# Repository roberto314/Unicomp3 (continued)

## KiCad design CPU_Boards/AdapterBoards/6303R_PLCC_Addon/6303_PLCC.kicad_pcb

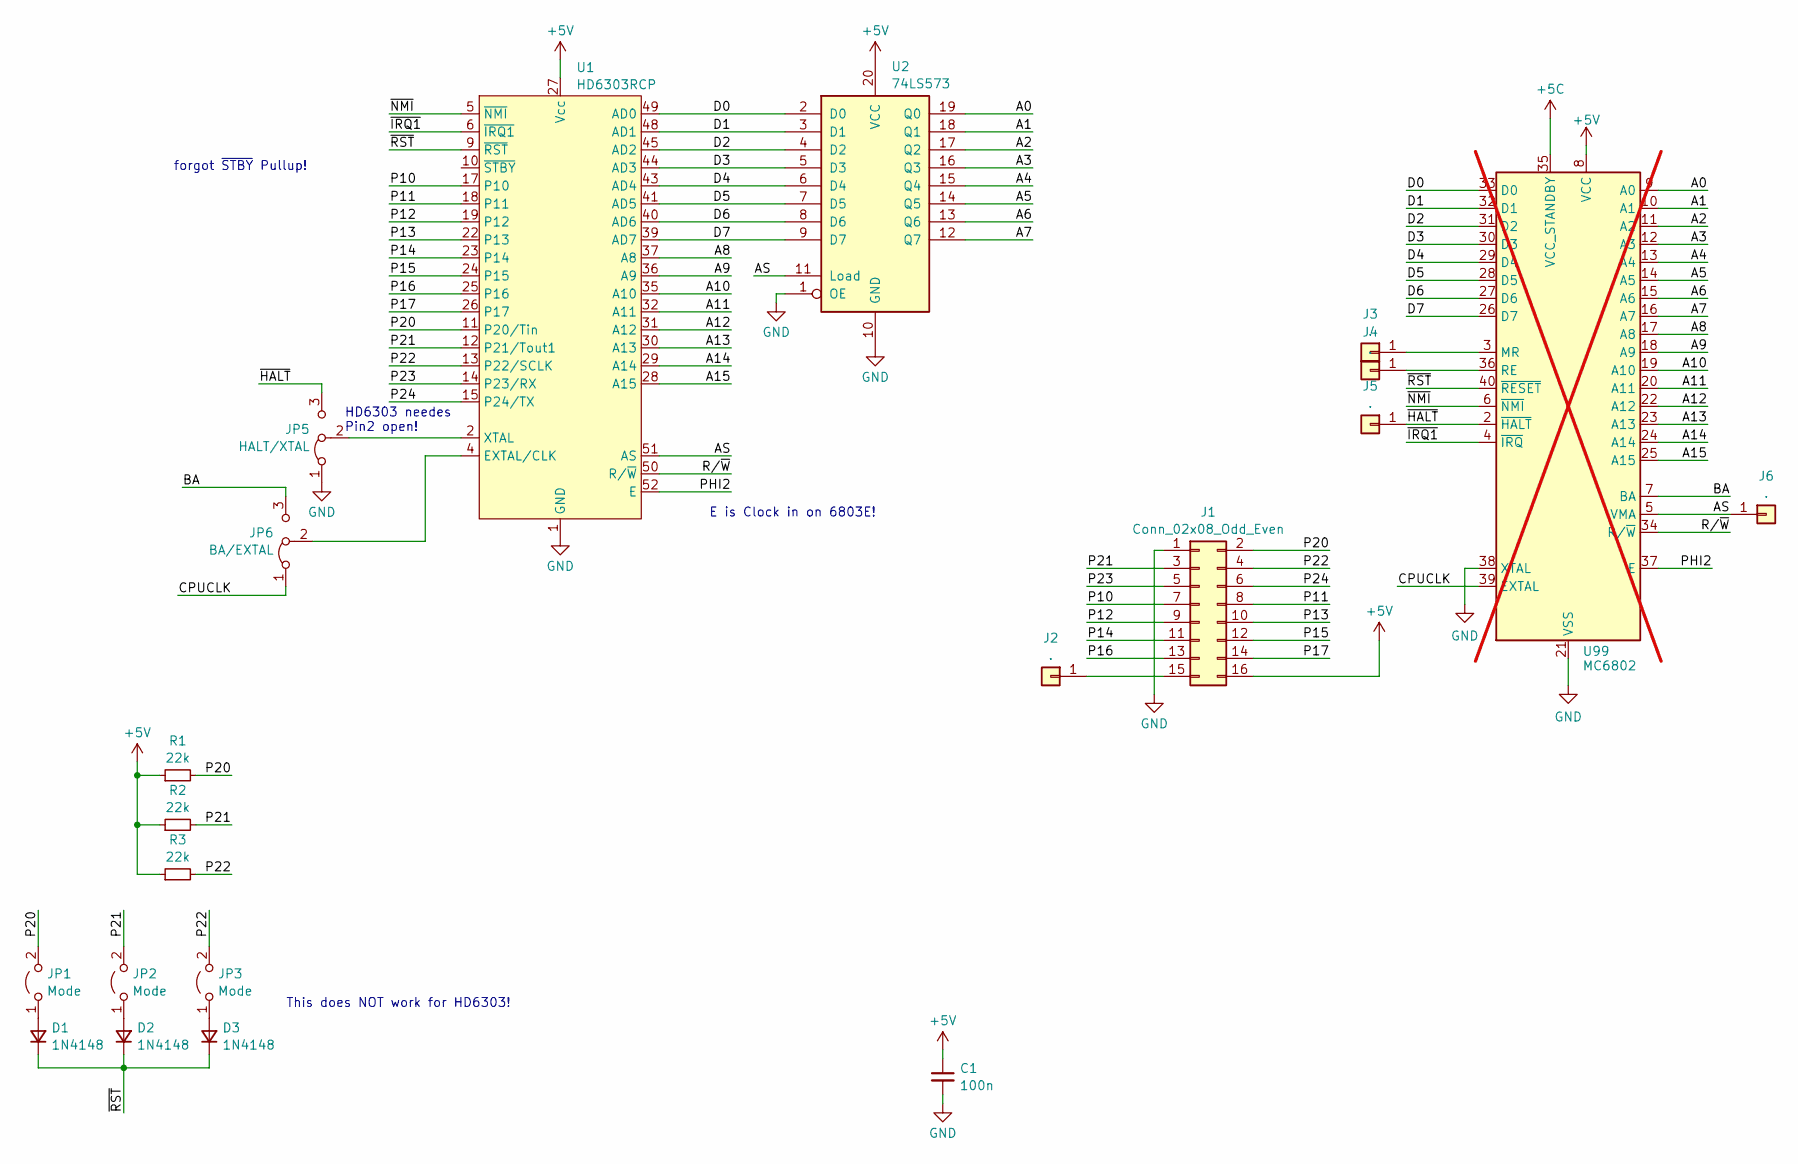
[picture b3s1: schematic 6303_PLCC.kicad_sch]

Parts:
C1: 100n; C_1206_3216Metric_Pad1.33x1.80mm_HandSolder
D1, D2, D3: 1N4148; D_1206_3216Metric_Pad1.42x1.75mm_HandSolder
J1: Conn_02x08_Odd_Even; PinHeader_2x08_P2.54mm_Horizontal
J2, J3, J4, J5, J6: .; PinHeader_1x01_P2.00mm_Vertical
JP1, JP2, JP3: Mode; PinHeader_1x02_P2.54mm_Vertical
JP5: HALT/XTAL; PinHeader_1x03_P2.54mm_Vertical
JP6: BA/EXTAL; PinHeader_1x03_P2.54mm_Vertical
R1, R2, R3: 22k; R_1206_3216Metric_Pad1.30x1.75mm_HandSolder
U1: HD6303RCP; PLCC-52_SMD-Socket
U2: 74LS573; DIP-20_W7.62mm_Socket_LongPads
U99: MC6802; DIP-40_W15.24mm; not fitted

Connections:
+5V: C1.1, J1.16, R1.1, R2.1, R3.1, U1.27 (Vcc), U2.20 (VCC); also elsewhere on the board
/A0: U2.19 (Q0); also elsewhere on the board
/A1: U2.18 (Q1); also elsewhere on the board
/A2: U2.17 (Q2); also elsewhere on the board
/A3: U2.16 (Q3); also elsewhere on the board
/A4: U2.15 (Q4); also elsewhere on the board
/A5: U2.14 (Q5); also elsewhere on the board
/A6: U2.13 (Q6); also elsewhere on the board
/A7: U2.12 (Q7); also elsewhere on the board
/A8: U1.37 (A8); also elsewhere on the board
/A9: U1.36 (A9); also elsewhere on the board
/A10: U1.35 (A10); also elsewhere on the board
/A11: U1.32 (A11); also elsewhere on the board
/A12: U1.31 (A12); also elsewhere on the board
/A13: U1.30 (A13); also elsewhere on the board
/A14: U1.29 (A14); also elsewhere on the board
/A15: U1.28 (A15); also elsewhere on the board
/AS: J6.1, U1.51 (AS), U2.11 (Load); also elsewhere on the board
/BA: JP6.3 (B); also elsewhere on the board
/CPUCLK: JP6.1 (A); also elsewhere on the board
/D0: U1.49 (AD0), U2.2 (D0); also elsewhere on the board
/D1: U1.48 (AD1), U2.3 (D1); also elsewhere on the board
/D2: U1.45 (AD2), U2.4 (D2); also elsewhere on the board
/D3: U1.44 (AD3), U2.5 (D3); also elsewhere on the board
/D4: U1.43 (AD4), U2.6 (D4); also elsewhere on the board
/D5: U1.41 (AD5), U2.7 (D5); also elsewhere on the board
/D6: U1.40 (AD6), U2.8 (D6); also elsewhere on the board
/D7: U1.39 (AD7), U2.9 (D7); also elsewhere on the board
/P10: J1.7, U1.17 (P10)
/P11: J1.8, U1.18 (P11)
/P12: J1.9, U1.19 (P12)
/P13: J1.10, U1.22 (P13)
/P14: J1.11, U1.23 (P14)
/P15: J1.12, U1.24 (P15)
/P16: J1.13, U1.25 (P16)
/P17: J1.14, U1.26 (P17)
/P20: J1.2, JP1.2 (B), R1.2, U1.11 (P20/Tin)
/P21: J1.3, JP2.2 (B), R2.2, U1.12 (P21/Tout1)
/P22: J1.4, JP3.2 (B), R3.2, U1.13 (P22/SCLK)
/P23: J1.5, U1.14 (P23/RX)
/P24: J1.6, U1.15 (P24/TX)
/PHI2: U1.52 (E); also elsewhere on the board
/R/~W: U1.50 (R/~W); also elsewhere on the board
/~HALT: J5.1, JP5.3 (B); also elsewhere on the board
/~IRQ1: U1.6 (~IRQ1); also elsewhere on the board
/~NMI: U1.5 (~NMI); also elsewhere on the board
/~RST: D1.1 (K), D2.1 (K), D3.1 (K), U1.9 (~RST); also elsewhere on the board
GND: C1.2, J1.1, JP5.1 (A), U1.1 (GND), U2.1 (OE), U2.10 (GND); also elsewhere on the board
unnamed: D1.2 (A), JP1.1 (A)
unnamed: D2.2 (A), JP2.1 (A)
unnamed: D3.2 (A), JP3.1 (A)
unnamed: J1.15, J2.1
unnamed 53: J3.1; also elsewhere on the board
unnamed 54: J4.1; also elsewhere on the board
unnamed: JP5.2 (C), U1.2 (XTAL)
unnamed: JP6.2 (C), U1.4 (EXTAL/CLK)

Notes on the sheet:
forgot ~{STBY} Pullup!
This does NOT work for HD6303!
E is Clock in on 6803E!
HD6303 needes Pin2 open!

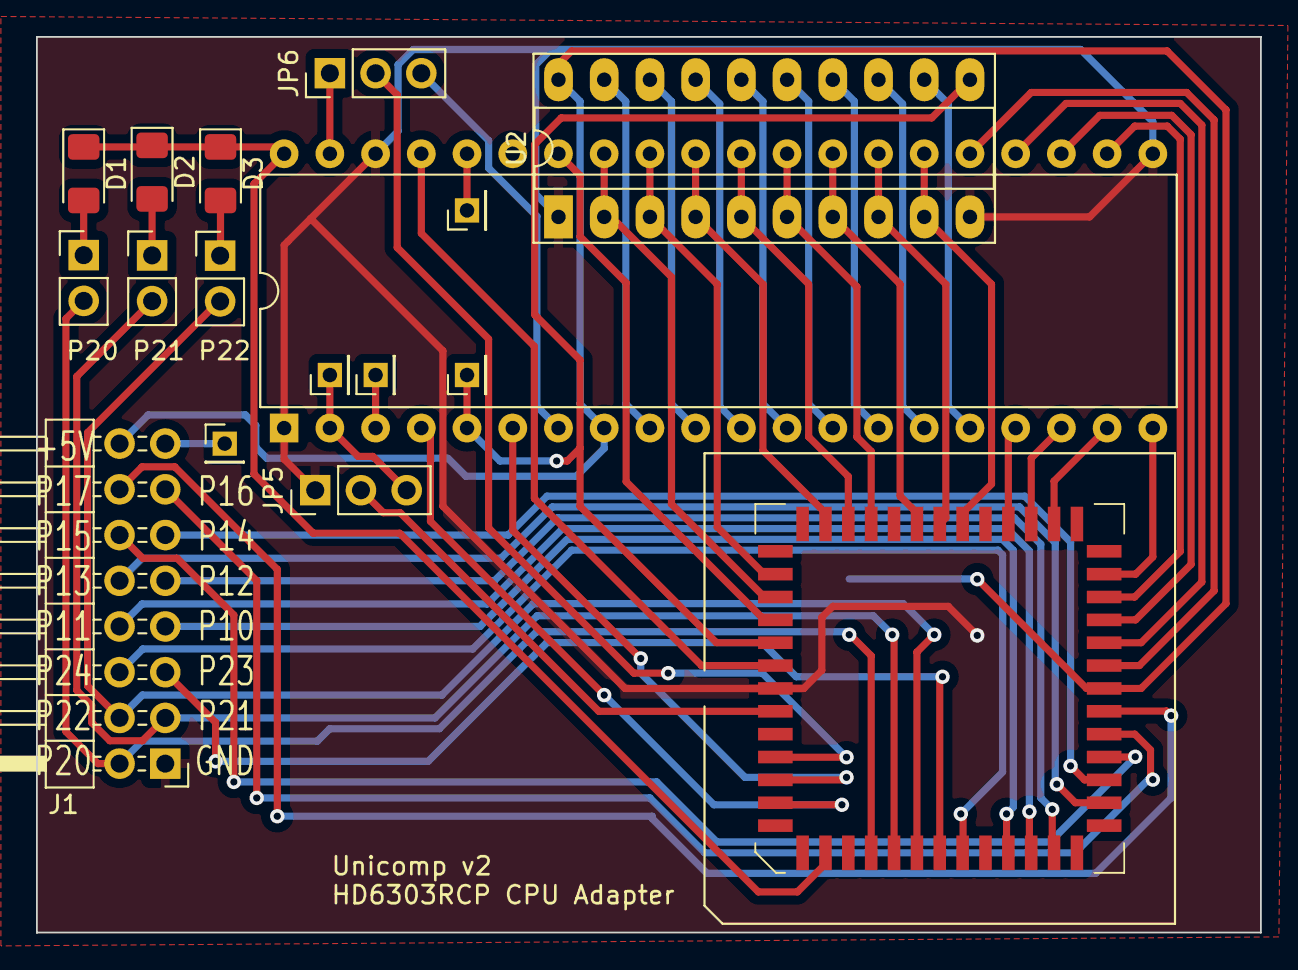
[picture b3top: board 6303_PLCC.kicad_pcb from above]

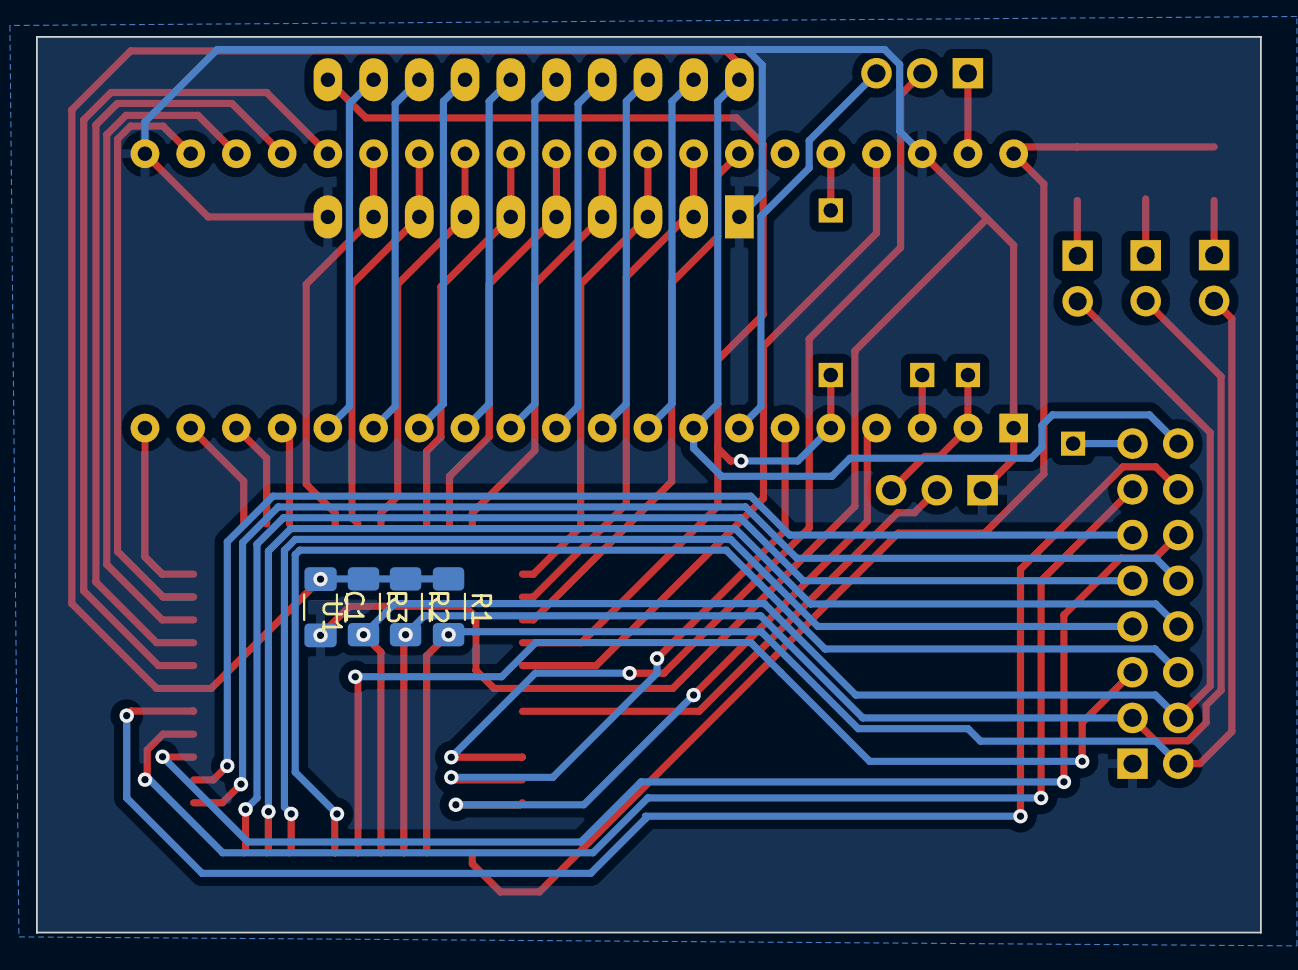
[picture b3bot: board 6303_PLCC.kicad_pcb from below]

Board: 2 copper layers, 68.0 x 49.8 mm, 21 parts (4 on the bottom side), 56 nets.

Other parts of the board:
U3: MC6802; DIP-40_W15.24mm

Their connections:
+5V: U3.8 (VCC); also elsewhere on the board
/A0: U3.9 (A0); also elsewhere on the board
/A1: U3.10 (A1); also elsewhere on the board
/A2: U3.11 (A2); also elsewhere on the board
/A3: U3.12 (A3); also elsewhere on the board
/A4: U3.13 (A4); also elsewhere on the board
/A5: U3.14 (A5); also elsewhere on the board
/A6: U3.15 (A6); also elsewhere on the board
/A7: U3.16 (A7); also elsewhere on the board
/A8: U3.17 (A8); also elsewhere on the board
/A9: U3.18 (A9); also elsewhere on the board
/A10: U3.19 (A10); also elsewhere on the board
/A11: U3.20 (A11); also elsewhere on the board
/A12: U3.22 (A12); also elsewhere on the board
/A13: U3.23 (A13); also elsewhere on the board
/A14: U3.24 (A14); also elsewhere on the board
/A15: U3.25 (A15); also elsewhere on the board
/AS: U3.5 (VMA); also elsewhere on the board
/BA: U3.7 (BA); also elsewhere on the board
/CPUCLK: U3.39 (EXTAL); also elsewhere on the board
/D0: U3.33 (D0); also elsewhere on the board
/D1: U3.32 (D1); also elsewhere on the board
/D2: U3.31 (D2); also elsewhere on the board
/D3: U3.30 (D3); also elsewhere on the board
/D4: U3.29 (D4); also elsewhere on the board
/D5: U3.28 (D5); also elsewhere on the board
/D6: U3.27 (D6); also elsewhere on the board
/D7: U3.26 (D7); also elsewhere on the board
/PHI2: U3.37 (E); also elsewhere on the board
/R/~W: U3.34 (R/~W); also elsewhere on the board
/~HALT: U3.2 (~HALT); also elsewhere on the board
/~IRQ1: U3.4 (~IRQ); also elsewhere on the board
/~NMI: U3.6 (~NMI); also elsewhere on the board
/~RST: U3.40 (~RESET); also elsewhere on the board
GND: U3.1 (VSS), U3.21 (VSS), U3.38 (XTAL); also elsewhere on the board
unnamed 53: U3.3 (MR); also elsewhere on the board
unnamed 54: U3.36 (RE); also elsewhere on the board

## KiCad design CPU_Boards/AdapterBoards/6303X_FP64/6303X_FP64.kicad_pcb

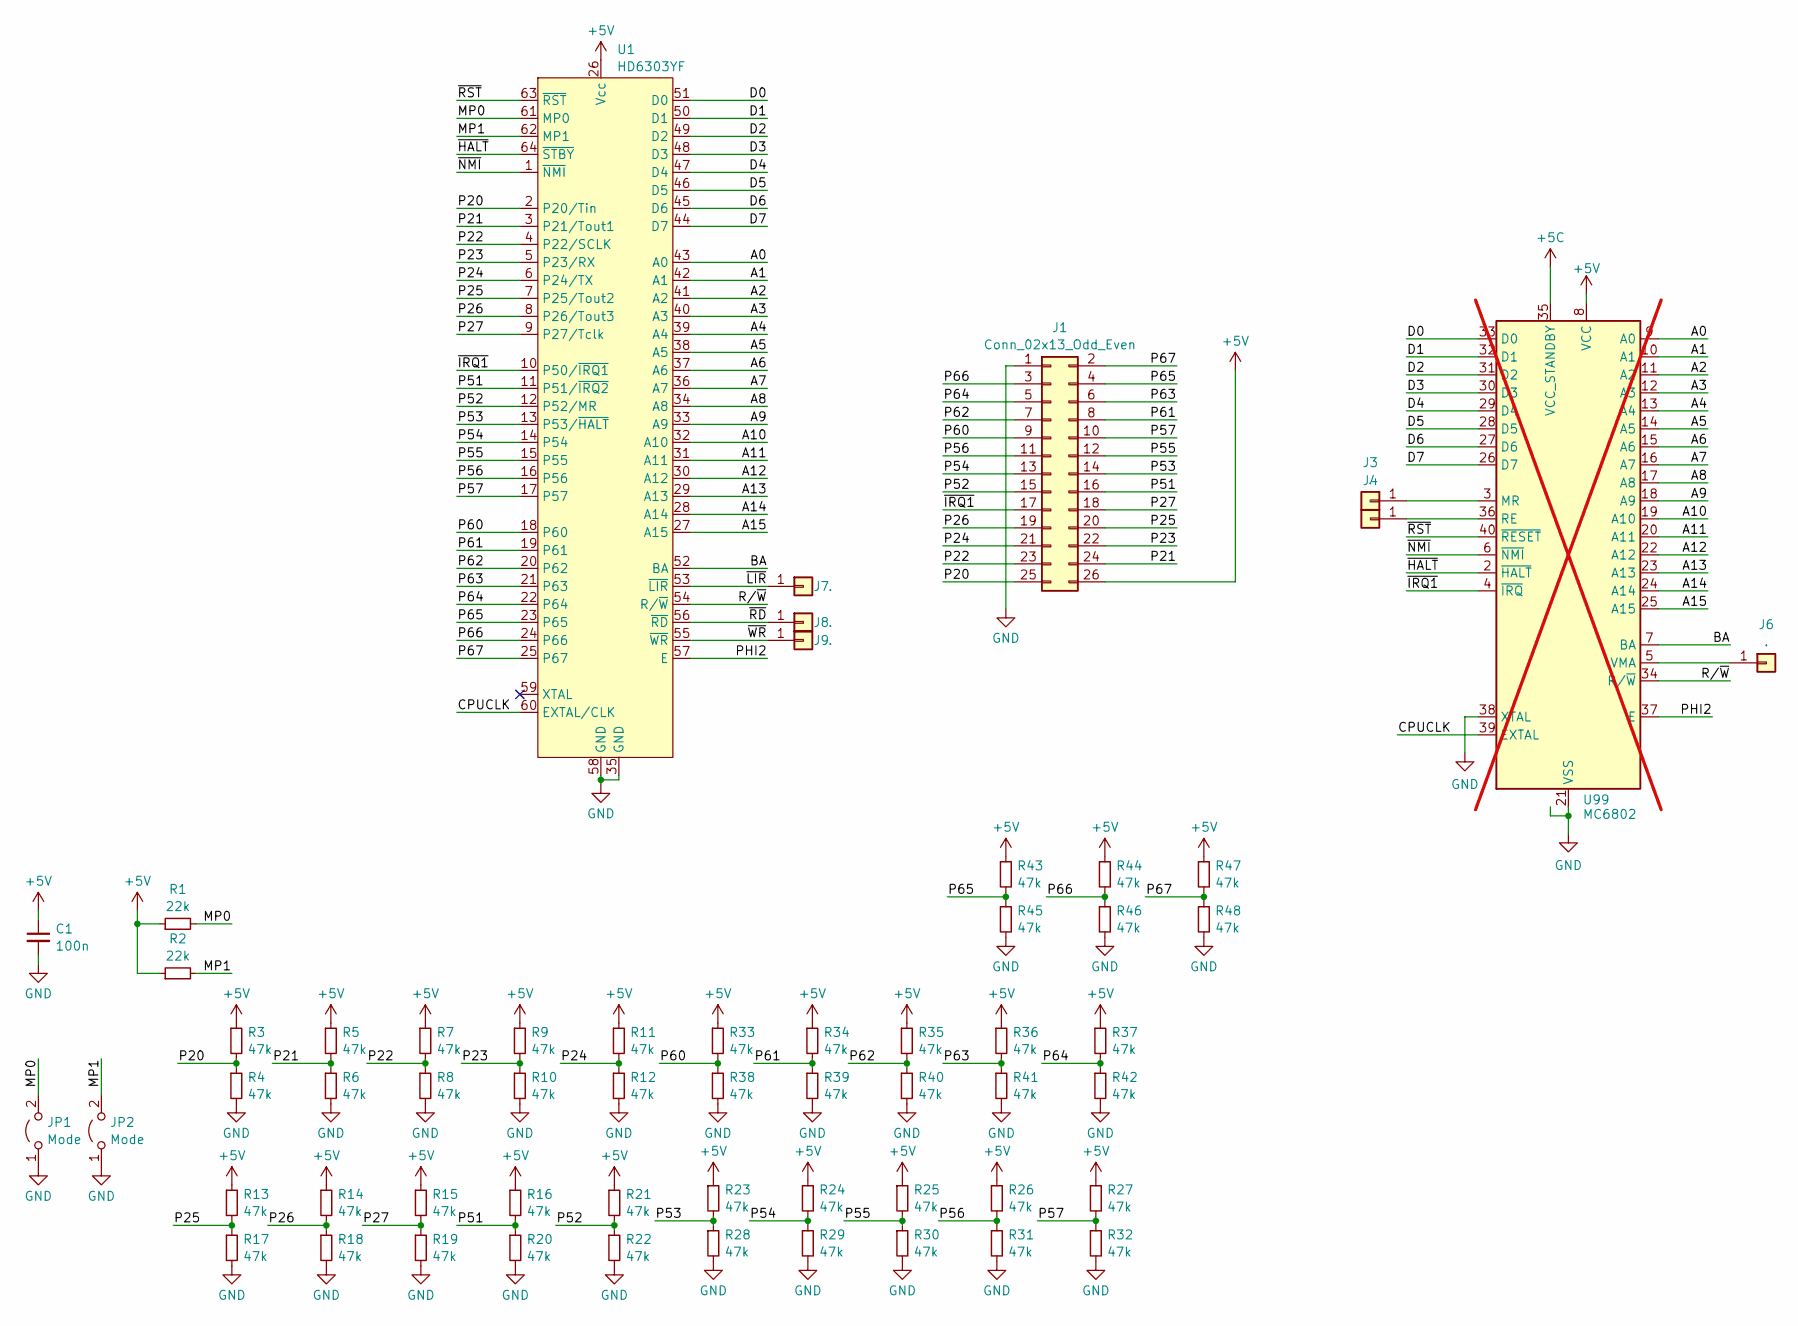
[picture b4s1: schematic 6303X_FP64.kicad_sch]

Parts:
C1: 100n; C_1206_3216Metric_Pad1.33x1.80mm_HandSolder
J1: Conn_02x13_Odd_Even; PinHeader_2x13_P2.54mm_Horizontal
J3, J4, J6, J7, J8, J9: .; PinHeader_1x01_P2.00mm_Vertical
JP1, JP2: Mode; PinHeader_1x02_P2.54mm_Vertical
R1, R2: 22k; R_1206_3216Metric_Pad1.30x1.75mm_HandSolder
R3, R4, R5, R6, R7, R8, R9, R10, R11, R12, R13, R14, R15, R16, R17, R18, R19, R20, R21, R22, R23, R24, R25, R26, R27, R28, R29, R30, R31, R32, R33, R34, R35, R36, R37, R38, R39, R40, R41, R42, R43, R44, R45, R46, R47, R48: 47k; R_1206_3216Metric_Pad1.30x1.75mm_HandSolder
U1: HD6303YF; QFP-64_14x20_Pitch1mm
U99: MC6802; DIP-40_W15.24mm; not fitted

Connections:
+5V: C1.1, J1.26, R1.1, R2.1, R3.1, R5.1, R7.1, R9.1, R11.1, R13.1, R14.1, R15.1, R16.1, R21.1, R23.1, R24.1, R25.1, R26.1, R27.1, R33.1, R34.1, R35.1, R36.1, R37.1, R43.1, R44.1, R47.1, U1.26 (Vcc); also elsewhere on the board
/A0: U1.43 (A0); also elsewhere on the board
/A1: U1.42 (A1); also elsewhere on the board
/A2: U1.41 (A2); also elsewhere on the board
/A3: U1.40 (A3); also elsewhere on the board
/A4: U1.39 (A4); also elsewhere on the board
/A5: U1.38 (A5); also elsewhere on the board
/A6: U1.37 (A6); also elsewhere on the board
/A7: U1.36 (A7); also elsewhere on the board
/A8: U1.34 (A8); also elsewhere on the board
/A9: U1.33 (A9); also elsewhere on the board
/A10: U1.32 (A10); also elsewhere on the board
/A11: U1.31 (A11); also elsewhere on the board
/A12: U1.30 (A12); also elsewhere on the board
/A13: U1.29 (A13); also elsewhere on the board
/A14: U1.28 (A14); also elsewhere on the board
/A15: U1.27 (A15); also elsewhere on the board
/BA: U1.52 (BA); also elsewhere on the board
/CPUCLK: U1.60 (EXTAL/CLK); also elsewhere on the board
/D0: U1.51 (D0); also elsewhere on the board
/D1: U1.50 (D1); also elsewhere on the board
/D2: U1.49 (D2); also elsewhere on the board
/D3: U1.48 (D3); also elsewhere on the board
/D4: U1.47 (D4); also elsewhere on the board
/D5: U1.46 (D5); also elsewhere on the board
/D6: U1.45 (D6); also elsewhere on the board
/D7: U1.44 (D7); also elsewhere on the board
/MP0: JP1.2 (B), R1.2, U1.61 (MP0)
/MP1: JP2.2 (B), R2.2, U1.62 (MP1)
/P20: J1.25, R3.2, R4.1, U1.2 (P20/Tin)
/P21: J1.24, R5.2, R6.1, U1.3 (P21/Tout1)
/P22: J1.23, R7.2, R8.1, U1.4 (P22/SCLK)
/P23: J1.22, R9.2, R10.1, U1.5 (P23/RX)
/P24: J1.21, R11.2, R12.1, U1.6 (P24/TX)
/P25: J1.20, R13.2, R17.1, U1.7 (P25/Tout2)
/P26: J1.19, R14.2, R18.1, U1.8 (P26/Tout3)
/P27: J1.18, R15.2, R19.1, U1.9 (P27/Tclk)
/P51: J1.16, R16.2, R20.1, U1.11 (P51/~IRQ2)
/P52: J1.15, R21.2, R22.1, U1.12 (P52/MR)
/P53: J1.14, R23.2, R28.1, U1.13 (P53/~HALT)
/P54: J1.13, R24.2, R29.1, U1.14 (P54)
/P55: J1.12, R25.2, R30.1, U1.15 (P55)
/P56: J1.11, R26.2, R31.1, U1.16 (P56)
/P57: J1.10, R27.2, R32.1, U1.17 (P57)
/P60: J1.9, R33.2, R38.1, U1.18 (P60)
/P61: J1.8, R34.2, R39.1, U1.19 (P61)
/P62: J1.7, R35.2, R40.1, U1.20 (P62)
/P63: J1.6, R36.2, R41.1, U1.21 (P63)
/P64: J1.5, R37.2, R42.1, U1.22 (P64)
/P65: J1.4, R43.2, R45.1, U1.23 (P65)
/P66: J1.3, R44.2, R46.1, U1.24 (P66)
/P67: J1.2, R47.2, R48.1, U1.25 (P67)
/PHI2: U1.57 (E); also elsewhere on the board
/R/~W: U1.54 (R/~W); also elsewhere on the board
/~HALT: U1.64 (~STBY); also elsewhere on the board
/~IRQ1: J1.17, U1.10 (P50/~IRQ1); also elsewhere on the board
/~LIR: J7.1, U1.53 (~LIR)
/~NMI: U1.1 (~NMI); also elsewhere on the board
/~RD: J8.1, U1.56 (~RD)
/~RST: U1.63 (~RST); also elsewhere on the board
/~WR: J9.1, U1.55 (~WR)
GND: C1.2, J1.1, JP1.1 (A), JP2.1 (A), R4.2, R6.2, R8.2, R10.2, R12.2, R17.2, R18.2, R19.2, R20.2, R22.2, R28.2, R29.2, R30.2, R31.2, R32.2, R38.2, R39.2, R40.2, R41.2, R42.2, R45.2, R46.2, R48.2, U1.35 (GND), U1.58 (GND); also elsewhere on the board
unnamed 63: J3.1; also elsewhere on the board
unnamed 64: J4.1; also elsewhere on the board
unnamed 65: J6.1; also elsewhere on the board

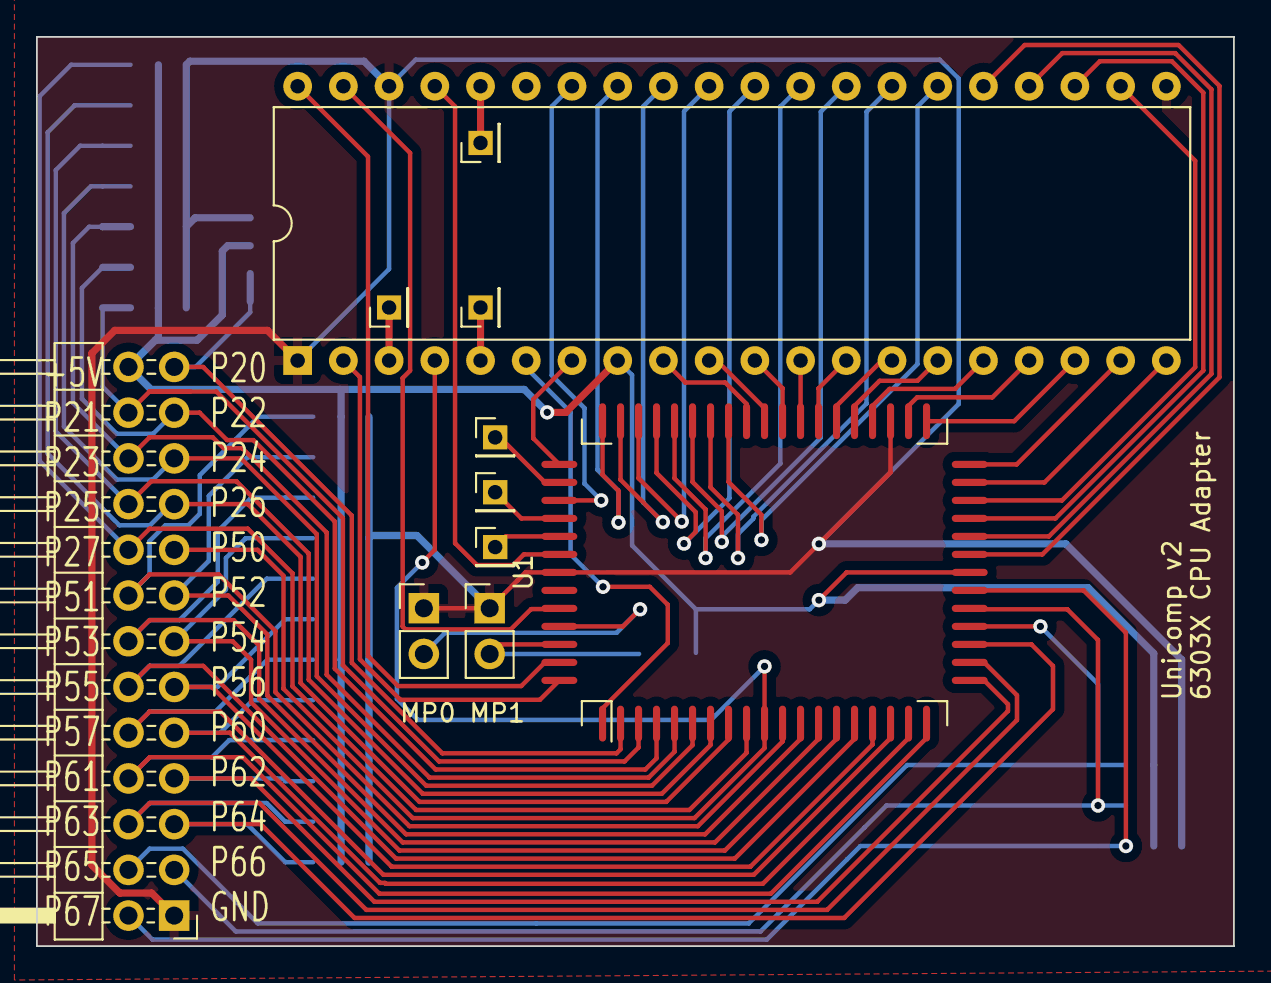
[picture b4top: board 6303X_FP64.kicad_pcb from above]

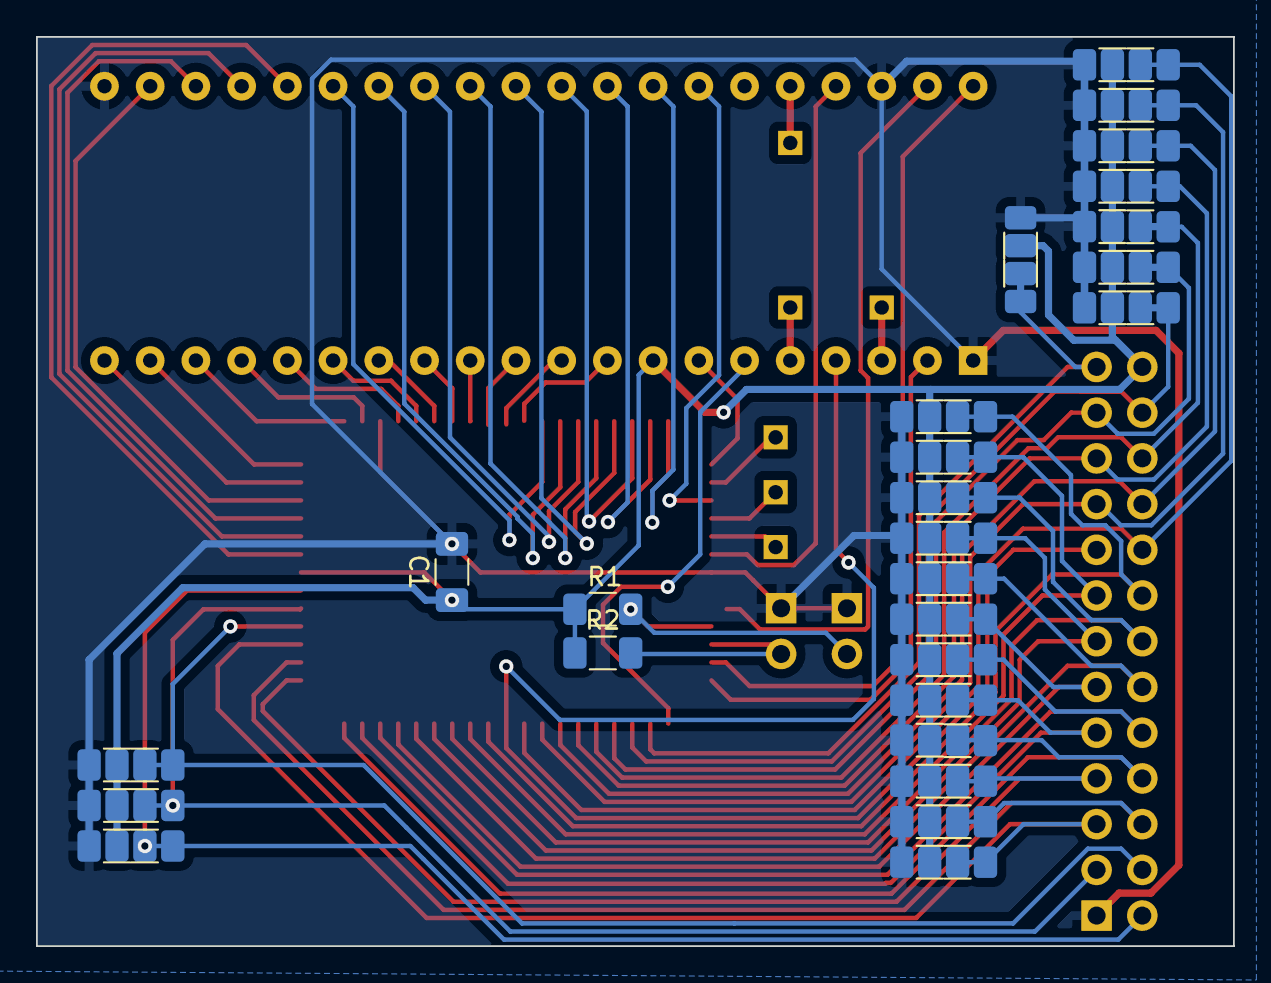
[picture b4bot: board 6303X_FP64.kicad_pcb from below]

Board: 2 copper layers, 66.5 x 50.5 mm, 60 parts (49 on the bottom side), 65 nets.

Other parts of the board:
U3: MC6802; DIP-40_W15.24mm

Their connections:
+5V: U3.8 (VCC); also elsewhere on the board
/A0: U3.9 (A0); also elsewhere on the board
/A1: U3.10 (A1); also elsewhere on the board
/A2: U3.11 (A2); also elsewhere on the board
/A3: U3.12 (A3); also elsewhere on the board
/A4: U3.13 (A4); also elsewhere on the board
/A5: U3.14 (A5); also elsewhere on the board
/A6: U3.15 (A6); also elsewhere on the board
/A7: U3.16 (A7); also elsewhere on the board
/A8: U3.17 (A8); also elsewhere on the board
/A9: U3.18 (A9); also elsewhere on the board
/A10: U3.19 (A10); also elsewhere on the board
/A11: U3.20 (A11); also elsewhere on the board
/A12: U3.22 (A12); also elsewhere on the board
/A13: U3.23 (A13); also elsewhere on the board
/A14: U3.24 (A14); also elsewhere on the board
/A15: U3.25 (A15); also elsewhere on the board
/BA: U3.7 (BA); also elsewhere on the board
/CPUCLK: U3.39 (EXTAL); also elsewhere on the board
/D0: U3.33 (D0); also elsewhere on the board
/D1: U3.32 (D1); also elsewhere on the board
/D2: U3.31 (D2); also elsewhere on the board
/D3: U3.30 (D3); also elsewhere on the board
/D4: U3.29 (D4); also elsewhere on the board
/D5: U3.28 (D5); also elsewhere on the board
/D6: U3.27 (D6); also elsewhere on the board
/D7: U3.26 (D7); also elsewhere on the board
/PHI2: U3.37 (E); also elsewhere on the board
/R/~W: U3.34 (R/~W); also elsewhere on the board
/~HALT: U3.2 (~HALT); also elsewhere on the board
/~IRQ1: U3.4 (~IRQ); also elsewhere on the board
/~NMI: U3.6 (~NMI); also elsewhere on the board
/~RST: U3.40 (~RESET); also elsewhere on the board
GND: U3.1 (VSS), U3.21 (VSS), U3.38 (XTAL); also elsewhere on the board
unnamed 63: U3.3 (MR); also elsewhere on the board
unnamed 64: U3.36 (RE); also elsewhere on the board
unnamed 65: U3.5 (VMA); also elsewhere on the board

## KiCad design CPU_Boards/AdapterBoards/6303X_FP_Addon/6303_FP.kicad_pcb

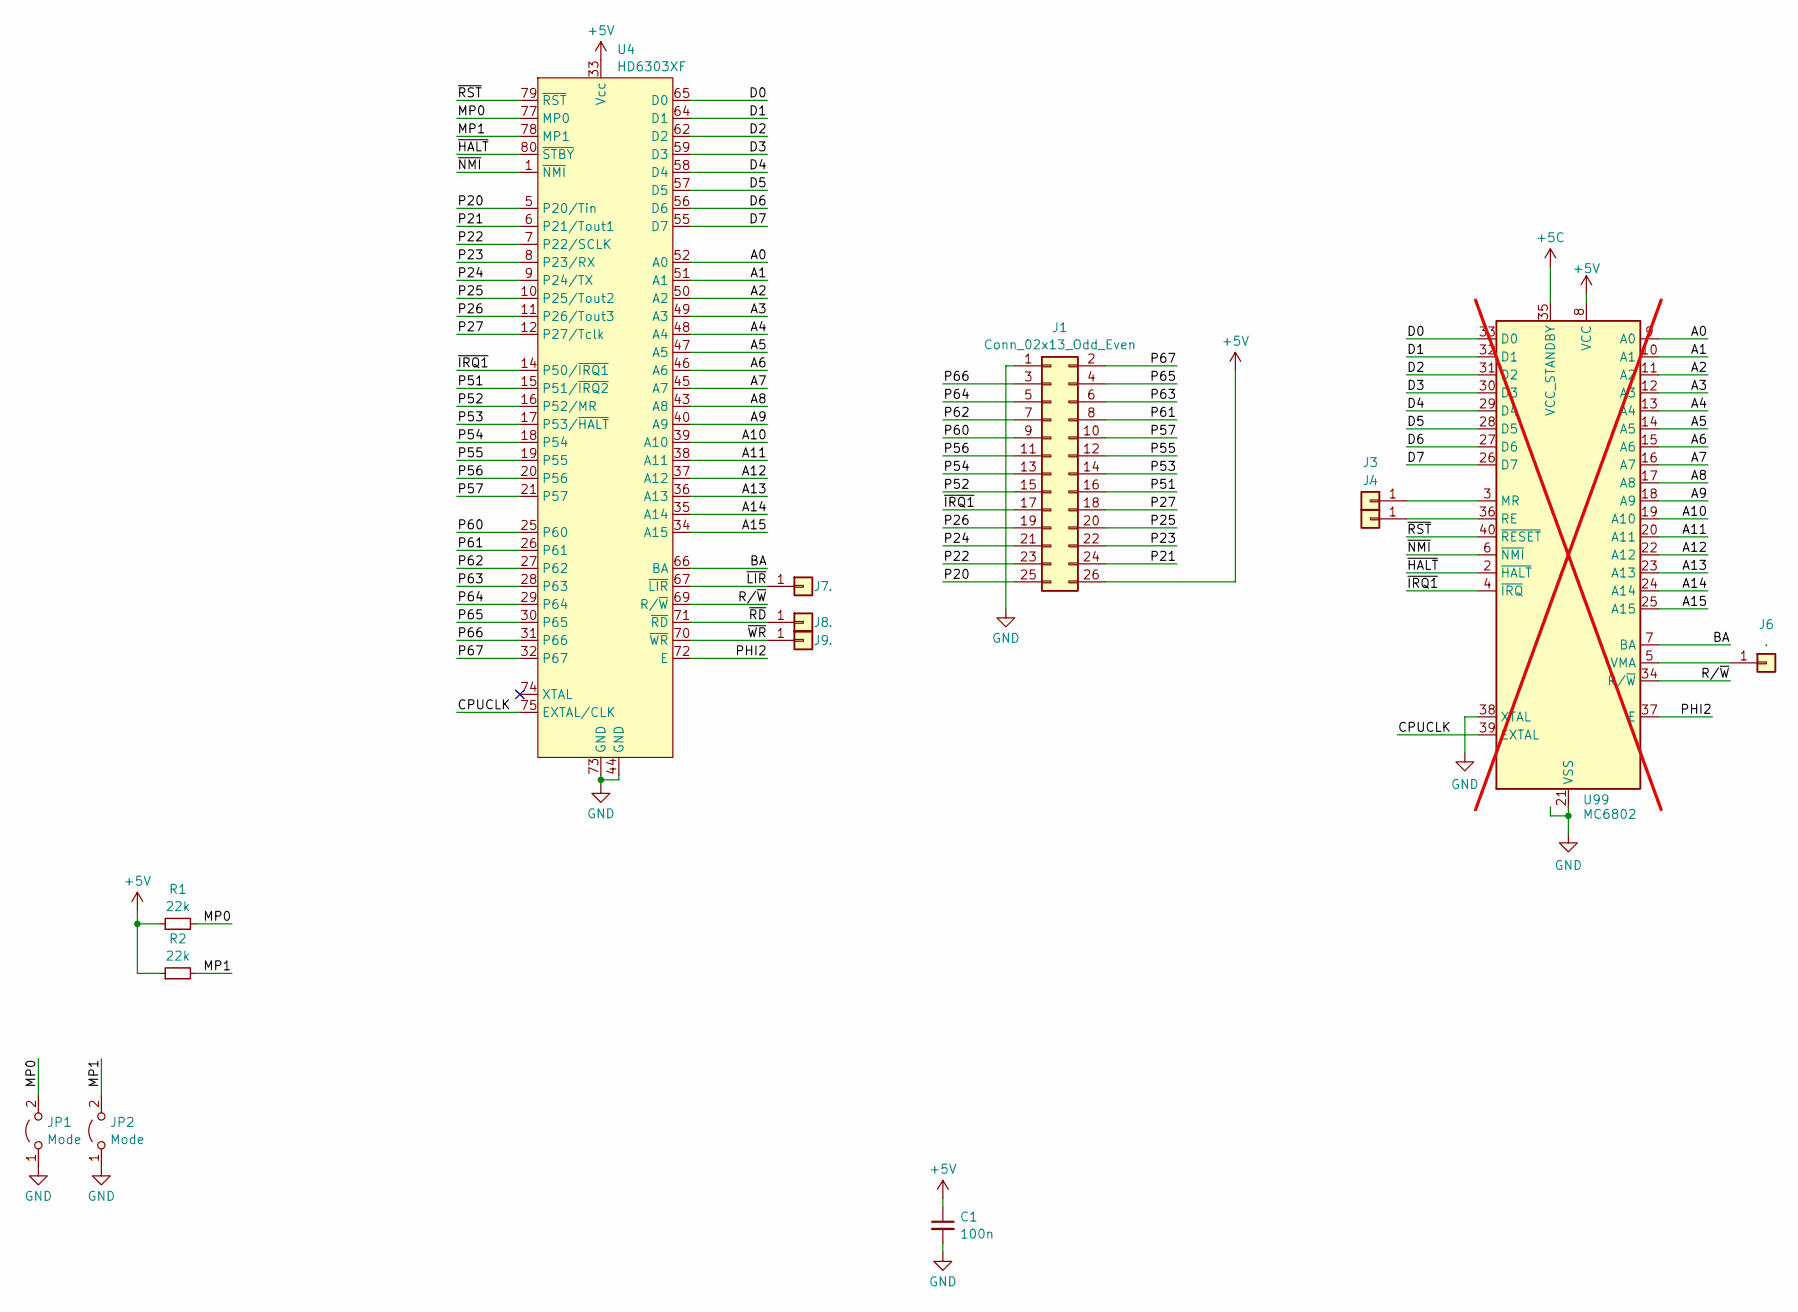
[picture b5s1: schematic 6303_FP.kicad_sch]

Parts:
C1: 100n; C_1206_3216Metric_Pad1.33x1.80mm_HandSolder
J1: Conn_02x13_Odd_Even; PinHeader_2x13_P2.54mm_Horizontal
J3, J4, J6, J7, J8, J9: .; PinHeader_1x01_P2.00mm_Vertical
JP1, JP2: Mode; PinHeader_1x02_P2.54mm_Vertical
R1, R2: 22k; R_1206_3216Metric_Pad1.30x1.75mm_HandSolder
U4: HD6303XF; PQFP-80_14x20mm_P0.8mm
U99: MC6802; DIP-40_W15.24mm; not fitted

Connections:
+5V: C1.1, J1.26, R1.1, R2.1, U4.33 (Vcc); also elsewhere on the board
/A0: U4.52 (A0); also elsewhere on the board
/A1: U4.51 (A1); also elsewhere on the board
/A2: U4.50 (A2); also elsewhere on the board
/A3: U4.49 (A3); also elsewhere on the board
/A4: U4.48 (A4); also elsewhere on the board
/A5: U4.47 (A5); also elsewhere on the board
/A6: U4.46 (A6); also elsewhere on the board
/A7: U4.45 (A7); also elsewhere on the board
/A8: U4.43 (A8); also elsewhere on the board
/A9: U4.40 (A9); also elsewhere on the board
/A10: U4.39 (A10); also elsewhere on the board
/A11: U4.38 (A11); also elsewhere on the board
/A12: U4.37 (A12); also elsewhere on the board
/A13: U4.36 (A13); also elsewhere on the board
/A14: U4.35 (A14); also elsewhere on the board
/A15: U4.34 (A15); also elsewhere on the board
/BA: U4.66 (BA); also elsewhere on the board
/CPUCLK: U4.75 (EXTAL/CLK); also elsewhere on the board
/D0: U4.65 (D0); also elsewhere on the board
/D1: U4.64 (D1); also elsewhere on the board
/D2: U4.62 (D2); also elsewhere on the board
/D3: U4.59 (D3); also elsewhere on the board
/D4: U4.58 (D4); also elsewhere on the board
/D5: U4.57 (D5); also elsewhere on the board
/D6: U4.56 (D6); also elsewhere on the board
/D7: U4.55 (D7); also elsewhere on the board
/MP0: JP1.2 (B), R1.2, U4.77 (MP0)
/MP1: JP2.2 (B), R2.2, U4.78 (MP1)
/P20: J1.25, U4.5 (P20/Tin)
/P21: J1.24, U4.6 (P21/Tout1)
/P22: J1.23, U4.7 (P22/SCLK)
/P23: J1.22, U4.8 (P23/RX)
/P24: J1.21, U4.9 (P24/TX)
/P25: J1.20, U4.10 (P25/Tout2)
/P26: J1.19, U4.11 (P26/Tout3)
/P27: J1.18, U4.12 (P27/Tclk)
/P51: J1.16, U4.15 (P51/~IRQ2)
/P52: J1.15, U4.16 (P52/MR)
/P53: J1.14, U4.17 (P53/~HALT)
/P54: J1.13, U4.18 (P54)
/P55: J1.12, U4.19 (P55)
/P56: J1.11, U4.20 (P56)
/P57: J1.10, U4.21 (P57)
/P60: J1.9, U4.25 (P60)
/P61: J1.8, U4.26 (P61)
/P62: J1.7, U4.27 (P62)
/P63: J1.6, U4.28 (P63)
/P64: J1.5, U4.29 (P64)
/P65: J1.4, U4.30 (P65)
/P66: J1.3, U4.31 (P66)
/P67: J1.2, U4.32 (P67)
/PHI2: U4.72 (E); also elsewhere on the board
/R/~W: U4.69 (R/~W); also elsewhere on the board
/~HALT: U4.80 (~STBY); also elsewhere on the board
/~IRQ1: J1.17, U4.14 (P50/~IRQ1); also elsewhere on the board
/~LIR: J7.1, U4.67 (~LIR)
/~NMI: U4.1 (~NMI); also elsewhere on the board
/~RD: J8.1, U4.71 (~RD)
/~RST: U4.79 (~RST); also elsewhere on the board
/~WR: J9.1, U4.70 (~WR)
GND: C1.2, J1.1, JP1.1 (A), JP2.1 (A), U4.44 (GND), U4.73 (GND); also elsewhere on the board
unnamed 63: J3.1; also elsewhere on the board
unnamed 64: J4.1; also elsewhere on the board
unnamed 65: J6.1; also elsewhere on the board
